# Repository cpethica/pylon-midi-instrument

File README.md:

# Pylon

MIDI solenoid driver board

Uses WEMOS D1 mini microcontroller

Accepts MIDI input and converts to MOSFET output up to 3A per channel

test

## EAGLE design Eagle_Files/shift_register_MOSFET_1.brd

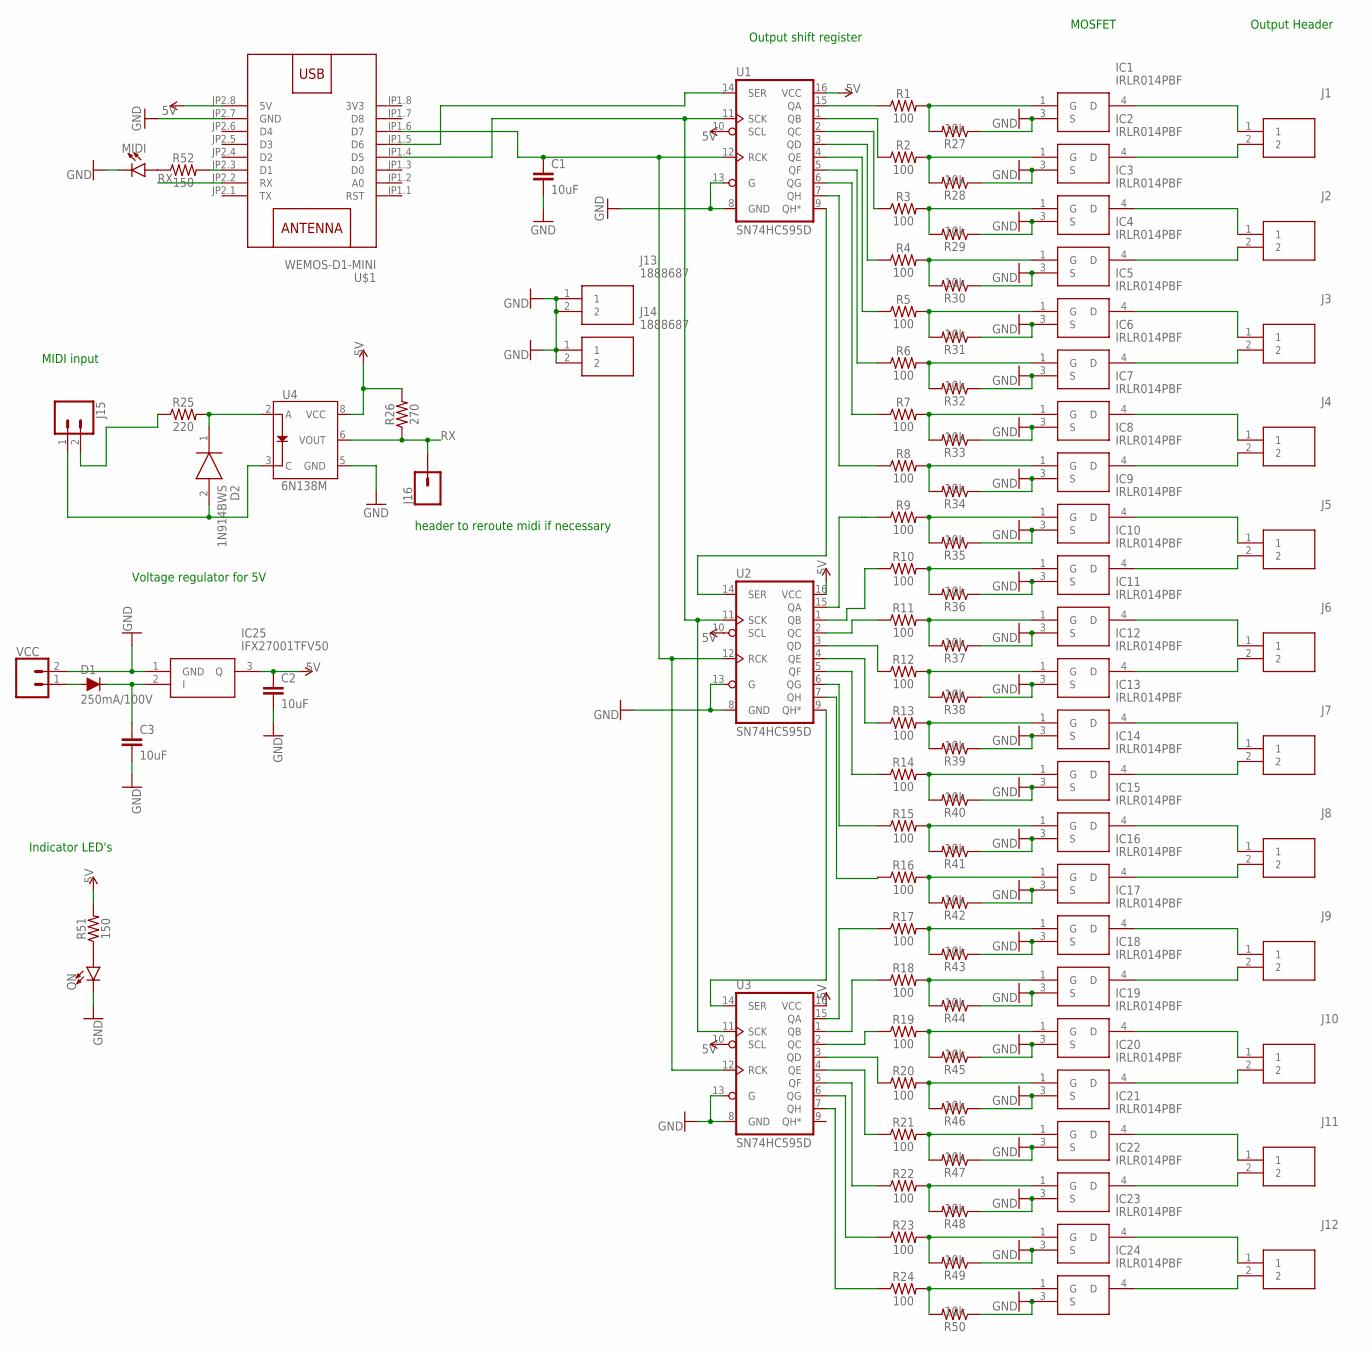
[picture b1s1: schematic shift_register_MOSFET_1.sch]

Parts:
C1, C2, C3: 10uF; C0805
D1: 250mA/100V; SOD-323
D2: 1N914BWS; SODFL2513X90N
IC1, IC2, IC3, IC4, IC5, IC6, IC7, IC8, IC9, IC10, IC11, IC12, IC13, IC14, IC15, IC16, IC17, IC18, IC19, IC20, IC21, IC22, IC23, IC24: IRLR014PBF; TO228P990X238-3N
IC25: IFX27001TFV50; PG-TO252-3-11
J1, J2, J3, J4, J5, J6, J7, J8, J9, J10, J11, J12, J13, J14: 1888687; SHDR2W90P0X508_1X2_1016X950X15
J15: CONN_02; 1X02
J16: CONN_01; 1X01
MIDI: LED3MM; LED_3MM
ON: LED3MM; LED_3MM
R1, R2, R3, R4, R5, R6, R7, R8, R9, R10, R11, R12, R13, R14, R15, R16, R17, R18, R19, R20, R21, R22, R23, R24: 100; 0805
R25: 220; 0805
R26: 270; 0805
R27, R28, R29, R30, R31, R32, R33, R34, R35, R36, R37, R38, R39, R40, R41, R42, R43, R44, R45, R46, R47, R48, R49, R50: 10k; 0805
R51, R52: 150; 0805
U1, U2, U3: SN74HC595D; SO16
U4: 6N138M; 8-SMD
U$1: WEMOS-D1-MINI
VCC: CONN_02; 1X02

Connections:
3V3: U$1.JP1.8 (3V3)
5V: C2.1, IC25.3 (Q), R26.2, R51.2, U1.10 (SCL), U1.16 (VCC), U2.10 (SCL), U2.16 (VCC), U3.10 (SCL), U3.16 (VCC), U4.8 (VCC), U$1.JP2.8 (5V)
GND: C1.2, C2.2, C3.2, IC1.3 (S), IC2.3 (S), IC3.3 (S), IC4.3 (S), IC5.3 (S), IC6.3 (S), IC7.3 (S), IC8.3 (S), IC9.3 (S), IC10.3 (S), IC11.3 (S), IC12.3 (S), IC13.3 (S), IC14.3 (S), IC15.3 (S), IC16.3 (S), IC17.3 (S), IC18.3 (S), IC19.3 (S), IC20.3 (S), IC21.3 (S), IC22.3 (S), IC23.3 (S), IC24.3 (S), IC25.1 (GND), J13.1, J13.2, J14.1, J14.2, MIDI.K (C), ON.K (C), R27.1, R28.1, R29.1, R30.1, R31.1, R32.1, R33.1, R34.1, R35.1, R36.1, R37.1, R38.1, R39.1, R40.1, R41.1, R42.1, R43.1, R44.1, R45.1, R46.1, R47.1, R48.1, R49.1, R50.1, U1.8 (GND), U1.13 (G), U2.8 (GND), U2.13 (G), U3.8 (GND), U3.13 (G), U4.5 (GND), U$1.JP2.7 (GND), VCC.2
unnamed: IC2.1 (G), R2.2, R28.2
unnamed: IC1.4 (D), J1.1
unnamed: R1.1, U1.15 (QA)
unnamed: D1.A, VCC.1
unnamed: R8.1, U1.7 (QH)
unnamed: R7.1, U1.6 (QG)
unnamed: R2.1, U1.1 (QB)
unnamed: R5.1, U1.4 (QE)
unnamed: R6.1, U1.5 (QF)
unnamed: R4.1, U1.3 (QD)
unnamed: R3.1, U1.2 (QC)
unnamed: IC3.1 (G), R3.2, R29.2
unnamed: IC4.1 (G), R4.2, R30.2
unnamed: IC5.1 (G), R5.2, R31.2
unnamed: IC6.1 (G), R6.2, R32.2
unnamed: IC2.4 (D), J1.2
unnamed: IC7.1 (G), R7.2, R33.2
unnamed: IC8.1 (G), R8.2, R34.2
unnamed: IC1.1 (G), R1.2, R27.2
unnamed: C3.1, D1.C, IC25.2 (I)
unnamed: U1.9 (QH*), U2.14 (SER)
unnamed: U1.11 (SCK), U2.11 (SCK), U3.11 (SCK), U$1.JP1.4 (D5)
unnamed: C1.1, U1.12 (RCK), U2.12 (RCK), U3.12 (RCK), U$1.JP1.6 (D7)
unnamed: U1.14 (SER), U$1.JP1.5 (D6)
unnamed: IC3.4 (D), J2.1
unnamed: R12.1, U2.3 (QD)
unnamed: R11.1, U2.2 (QC)
unnamed: ON.A, R51.1
unnamed: R9.1, U2.15 (QA)
unnamed: IC9.1 (G), R9.2, R35.2
unnamed: IC10.1 (G), R10.2, R36.2
unnamed: IC11.1 (G), R11.2, R37.2
unnamed: IC12.1 (G), R12.2, R38.2
unnamed: IC13.1 (G), R13.2, R39.2
unnamed: R13.1, U2.4 (QE)
unnamed: R14.1, U2.5 (QF)
unnamed: IC4.4 (D), J2.2
unnamed: R15.1, U2.6 (QG)
unnamed: R16.1, U2.7 (QH)
unnamed: U2.9 (QH*), U3.14 (SER)
unnamed: J15.2, R25.1
unnamed: IC19.1 (G), R19.2, R45.2
unnamed: IC20.1 (G), R20.2, R46.2
unnamed: D2.1 (K), R25.2, U4.2 (A)
unnamed: D2.2 (A), J15.1, U4.3 (C)
unnamed: R17.1, U3.15 (QA)
unnamed: R18.1, U3.1 (QB)
unnamed: IC21.1 (G), R21.2, R47.2
unnamed: IC22.1 (G), R22.2, R48.2
unnamed: IC23.1 (G), R23.2, R49.2
unnamed: IC24.1 (G), R24.2, R50.2
unnamed: IC14.1 (G), R14.2, R40.2
unnamed: IC15.1 (G), R15.2, R41.2
unnamed: IC16.1 (G), R16.2, R42.2
unnamed: IC17.1 (G), R17.2, R43.2
unnamed: IC18.1 (G), R18.2, R44.2
unnamed: IC5.4 (D), J3.1
unnamed: IC6.4 (D), J3.2
unnamed: IC7.4 (D), J4.1
unnamed: IC8.4 (D), J4.2
unnamed: IC9.4 (D), J5.1
unnamed: IC10.4 (D), J5.2
unnamed: IC11.4 (D), J6.1
unnamed: IC12.4 (D), J6.2
unnamed: IC13.4 (D), J7.1
unnamed: IC14.4 (D), J7.2
unnamed: IC15.4 (D), J8.1
unnamed: IC16.4 (D), J8.2
unnamed: IC17.4 (D), J9.1
unnamed: IC18.4 (D), J9.2
unnamed: IC19.4 (D), J10.1
unnamed: IC20.4 (D), J10.2
unnamed: IC21.4 (D), J11.1
unnamed: IC22.4 (D), J11.2
unnamed: IC23.4 (D), J12.1
unnamed: IC24.4 (D), J12.2
unnamed: R19.1, U3.2 (QC)
unnamed: R20.1, U3.3 (QD)
unnamed: R21.1, U3.4 (QE)
unnamed: R22.1, U3.5 (QF)
unnamed: R23.1, U3.6 (QG)
unnamed: R24.1, U3.7 (QH)
unnamed: R10.1, U2.1 (QB)
unnamed: MIDI.A, R52.1
unnamed: R52.2, U$1.JP2.3 (D1)
RX: J16.1, R26.1, U4.6 (VOUT), U$1.JP2.2 (RX)

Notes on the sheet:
Output shift register
Output Header
MOSFET
MIDI input
header to reroute midi if necessary
Voltage regulator for 5V
Indicator LED's

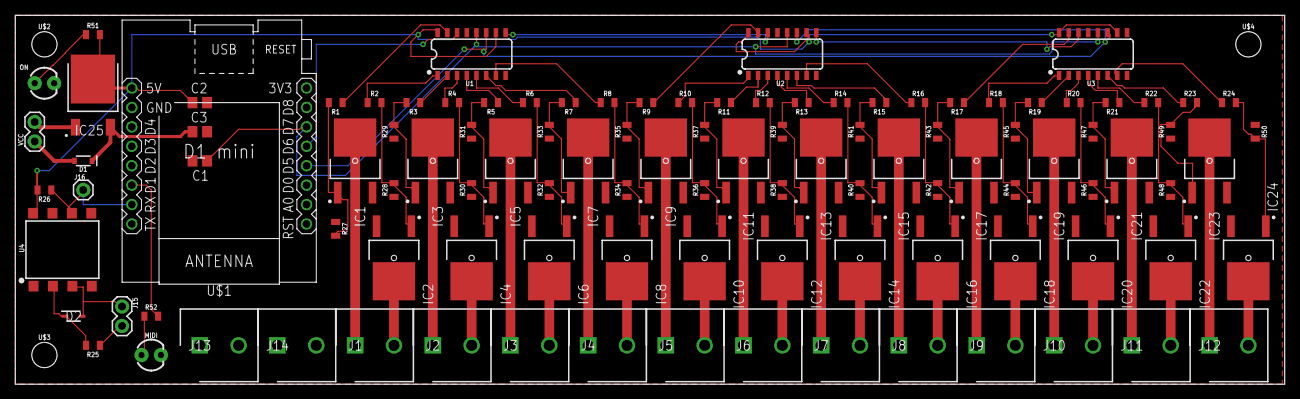
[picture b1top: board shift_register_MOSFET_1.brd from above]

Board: 2 copper layers, 166.0 x 48.2 mm, 109 parts (0 on the bottom side), 88 nets.

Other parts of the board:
U$2, U$3, U$4: STAND-OFF

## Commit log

2022-02-26 Added arduino libraries
2022-02-26 added eagle files and readme
2022-02-26 added images to readme
2022-02-26 added eagle files

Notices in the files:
parts and their libraries:
SparkFun-Resistors: Licensing: Creative Commons ShareAlike 4.0 International - https://creativecommons.org/licenses/by-sa/4.0
diy-modules: Released under the Creative Commons Attribution 4.0 International License: http://creativecommons.org/licenses/by/4.0
